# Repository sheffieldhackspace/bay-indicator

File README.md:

# display-infotec-bay-indicator

An Adafruit GFX compatible driver for the Infotec bay indicator AS1100-based dot matrix display.

## Hardware

* Display dimensions: 192 × 9
* Number of displays: 2
* Operating voltage: 3.3V
* Power voltage: 5V

### Prototype

### Schematic

See the [KiCad project](./kicad) for the full schematic.

### PCB Design

### PCB

## Installation

Add the following to your `platformio.ini`:

```ini
lib_deps =
    adafruit/Adafruit BusIO
    adafruit/Adafruit GFX Library
    https://github.com/sheffieldhackspace/display-infotec-bay-indicator
```

## Dependencies

* [Adafruit BusIO](https://github.com/adafruit/Adafruit_BusIO)
* [Adafruit GFX Library](https://github.com/adafruit/Adafruit-GFX-Library)
* ESP32 with FreeRTOS (required for the keepalive task)

## Usage

```cpp
#include <BayIndicator.h>

BayIndicator display1 = BayIndicator(D5, D6, D4);
BayIndicator display2 = BayIndicator(D8, D7, D9);

void setup() {
    delay(1000); // Give the display a moment to power up before configuring it

    display1.begin();
    display1.fillScreen(0);
    display1.setCursor(1, 1);
    display1.print("Sheffield");
    display1.display();

    display2.begin();
    display2.fillScreen(0);
    display2.setCursor(1, 1);
    display2.print("Hackspace");
    display2.display();
}

void loop() {
    // update displays as needed
    display1.display();
    display2.display();
}
```

Since `BayIndicator` inherits from `GFXcanvas1`, the full
[Adafruit GFX API](https://learn.adafruit.com/adafruit-gfx-graphics-library)
is available for drawing text, shapes, and bitmaps. Call `display.display()`
to flush the canvas to the hardware.

## Examples

Three examples are included in the `examples/` directory. To build and flash them, clone the repository and run:

```bash
# Show a hardware test pattern
pio run -t upload -e test

# Show a checkerboard pattern
pio run -t upload -e checkerboard

# Scroll two lines of text around the display
pio run -t upload -e movingwords
```

## Acknowledgements

Inspired by the works of [`alifeee`](https://github.com/alifeee/bus-signs) and
[`ConnectedHumber`](https://github.com/ConnectedHumber/Bus-Terminal-Signs).
The reverse engineering work of the display's segment layout and SPI protocol
was instrumental in the development of this library.

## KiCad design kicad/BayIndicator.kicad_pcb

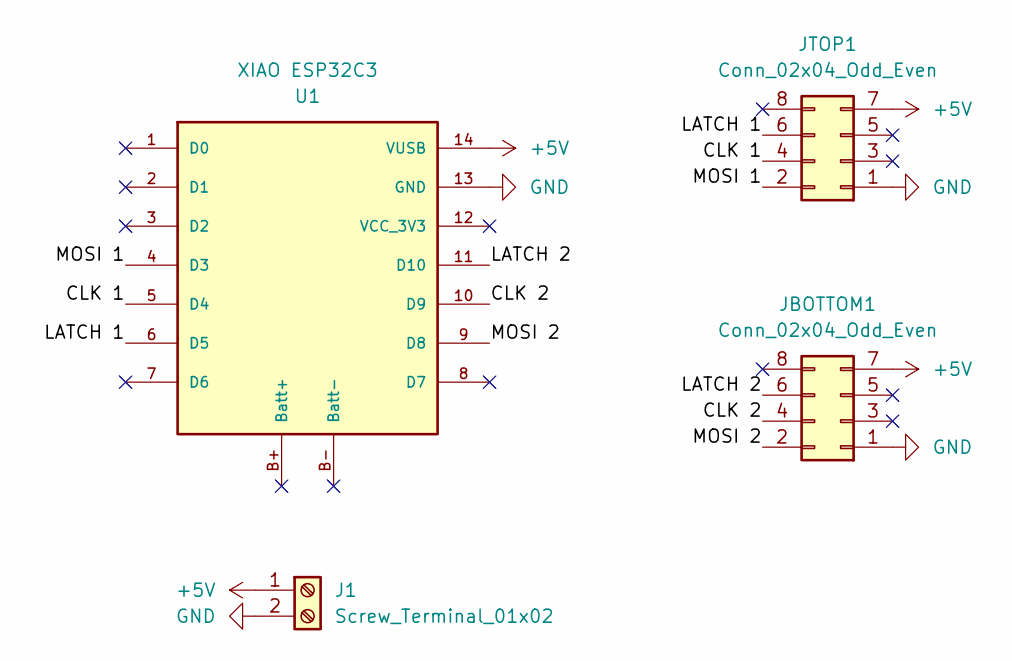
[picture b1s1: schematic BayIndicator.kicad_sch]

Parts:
J1: Screw_Terminal_01x02; TerminalBlock_MaiXu_MX126-5.0-02P_1x02_P5.00mm
JBOTTOM1: Conn_02x04_Odd_Even; IDC-Header_2x04_P2.54mm_Vertical
JTOP1: Conn_02x04_Odd_Even; IDC-Header_2x04_P2.54mm_Vertical
U1: XIAO ESP32C3; XIAO Seeed ESP32C3 DIP

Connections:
+5V: J1.1, JBOTTOM1.7, JTOP1.7, U1.14 (VUSB)
/CLK 1: JTOP1.4, U1.5 (D4)
/CLK 2: JBOTTOM1.4, U1.10 (D9)
/LATCH 1: JTOP1.6, U1.6 (D5)
/LATCH 2: JBOTTOM1.6, U1.11 (D10)
/MOSI 1: JTOP1.2, U1.4 (D3)
/MOSI 2: JBOTTOM1.2, U1.9 (D8)
GND: J1.2, JBOTTOM1.1, JTOP1.1, U1.13 (GND)

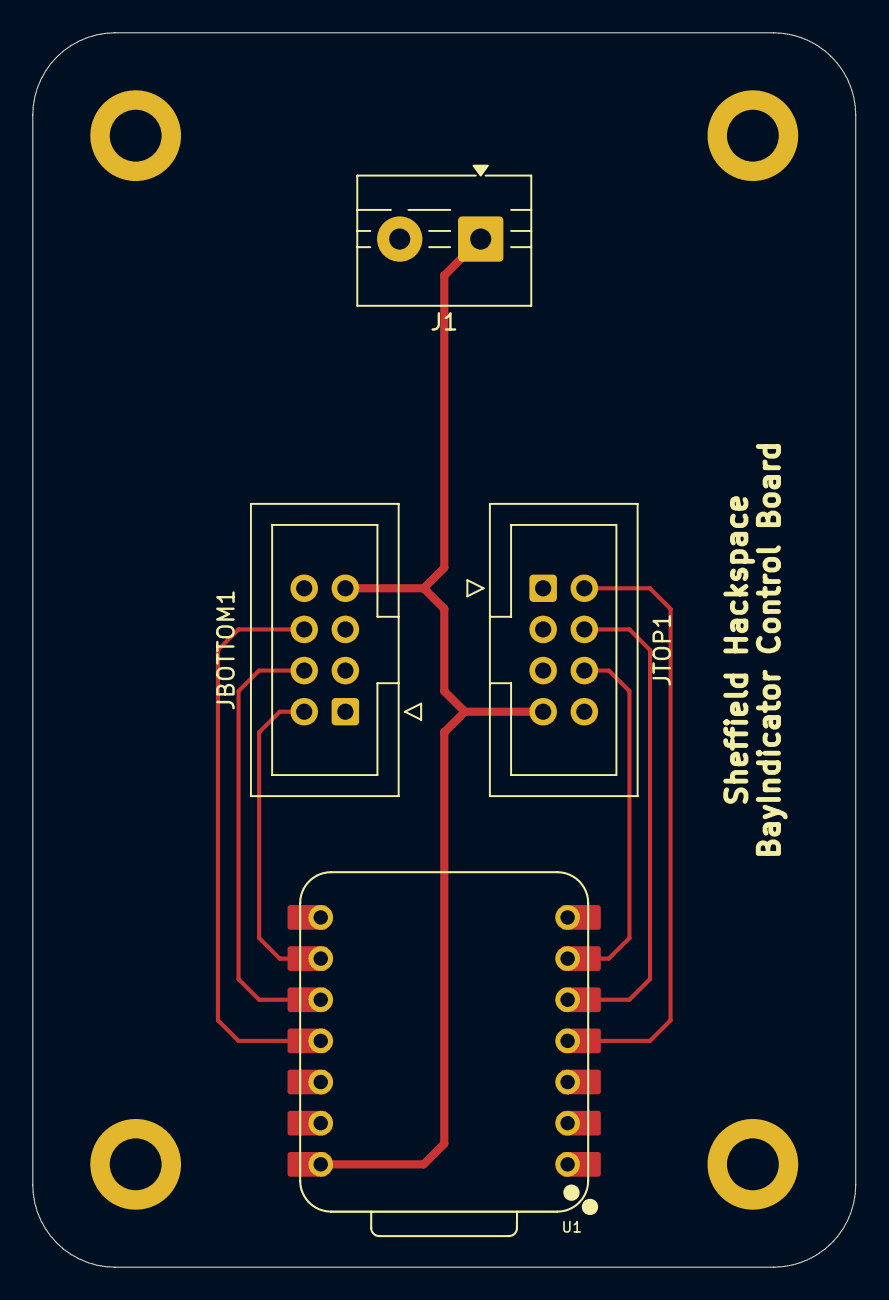
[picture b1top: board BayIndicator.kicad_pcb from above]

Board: 2 copper layers, 50.8 x 76.2 mm, 4 parts (0 on the bottom side), 8 nets.

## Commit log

2026-04-04 Adjust the examples to the new board layout
2026-04-04 Adjust the schematic to match the current state
2026-04-04 Reconnect to match the actual state
2026-04-20 Allow setting intensity in the begin method
2026-04-22 Create a PCB for the BayIndicator
2026-04-24 getRawPixel to support setRotation + fixed SPI configuration to match spec
2026-05-09 KiCAD 10.0
2026-05-09 PCB design
2026-05-16 Match the board layout
2026-05-16 Update photos
2026-05-16 3d models
